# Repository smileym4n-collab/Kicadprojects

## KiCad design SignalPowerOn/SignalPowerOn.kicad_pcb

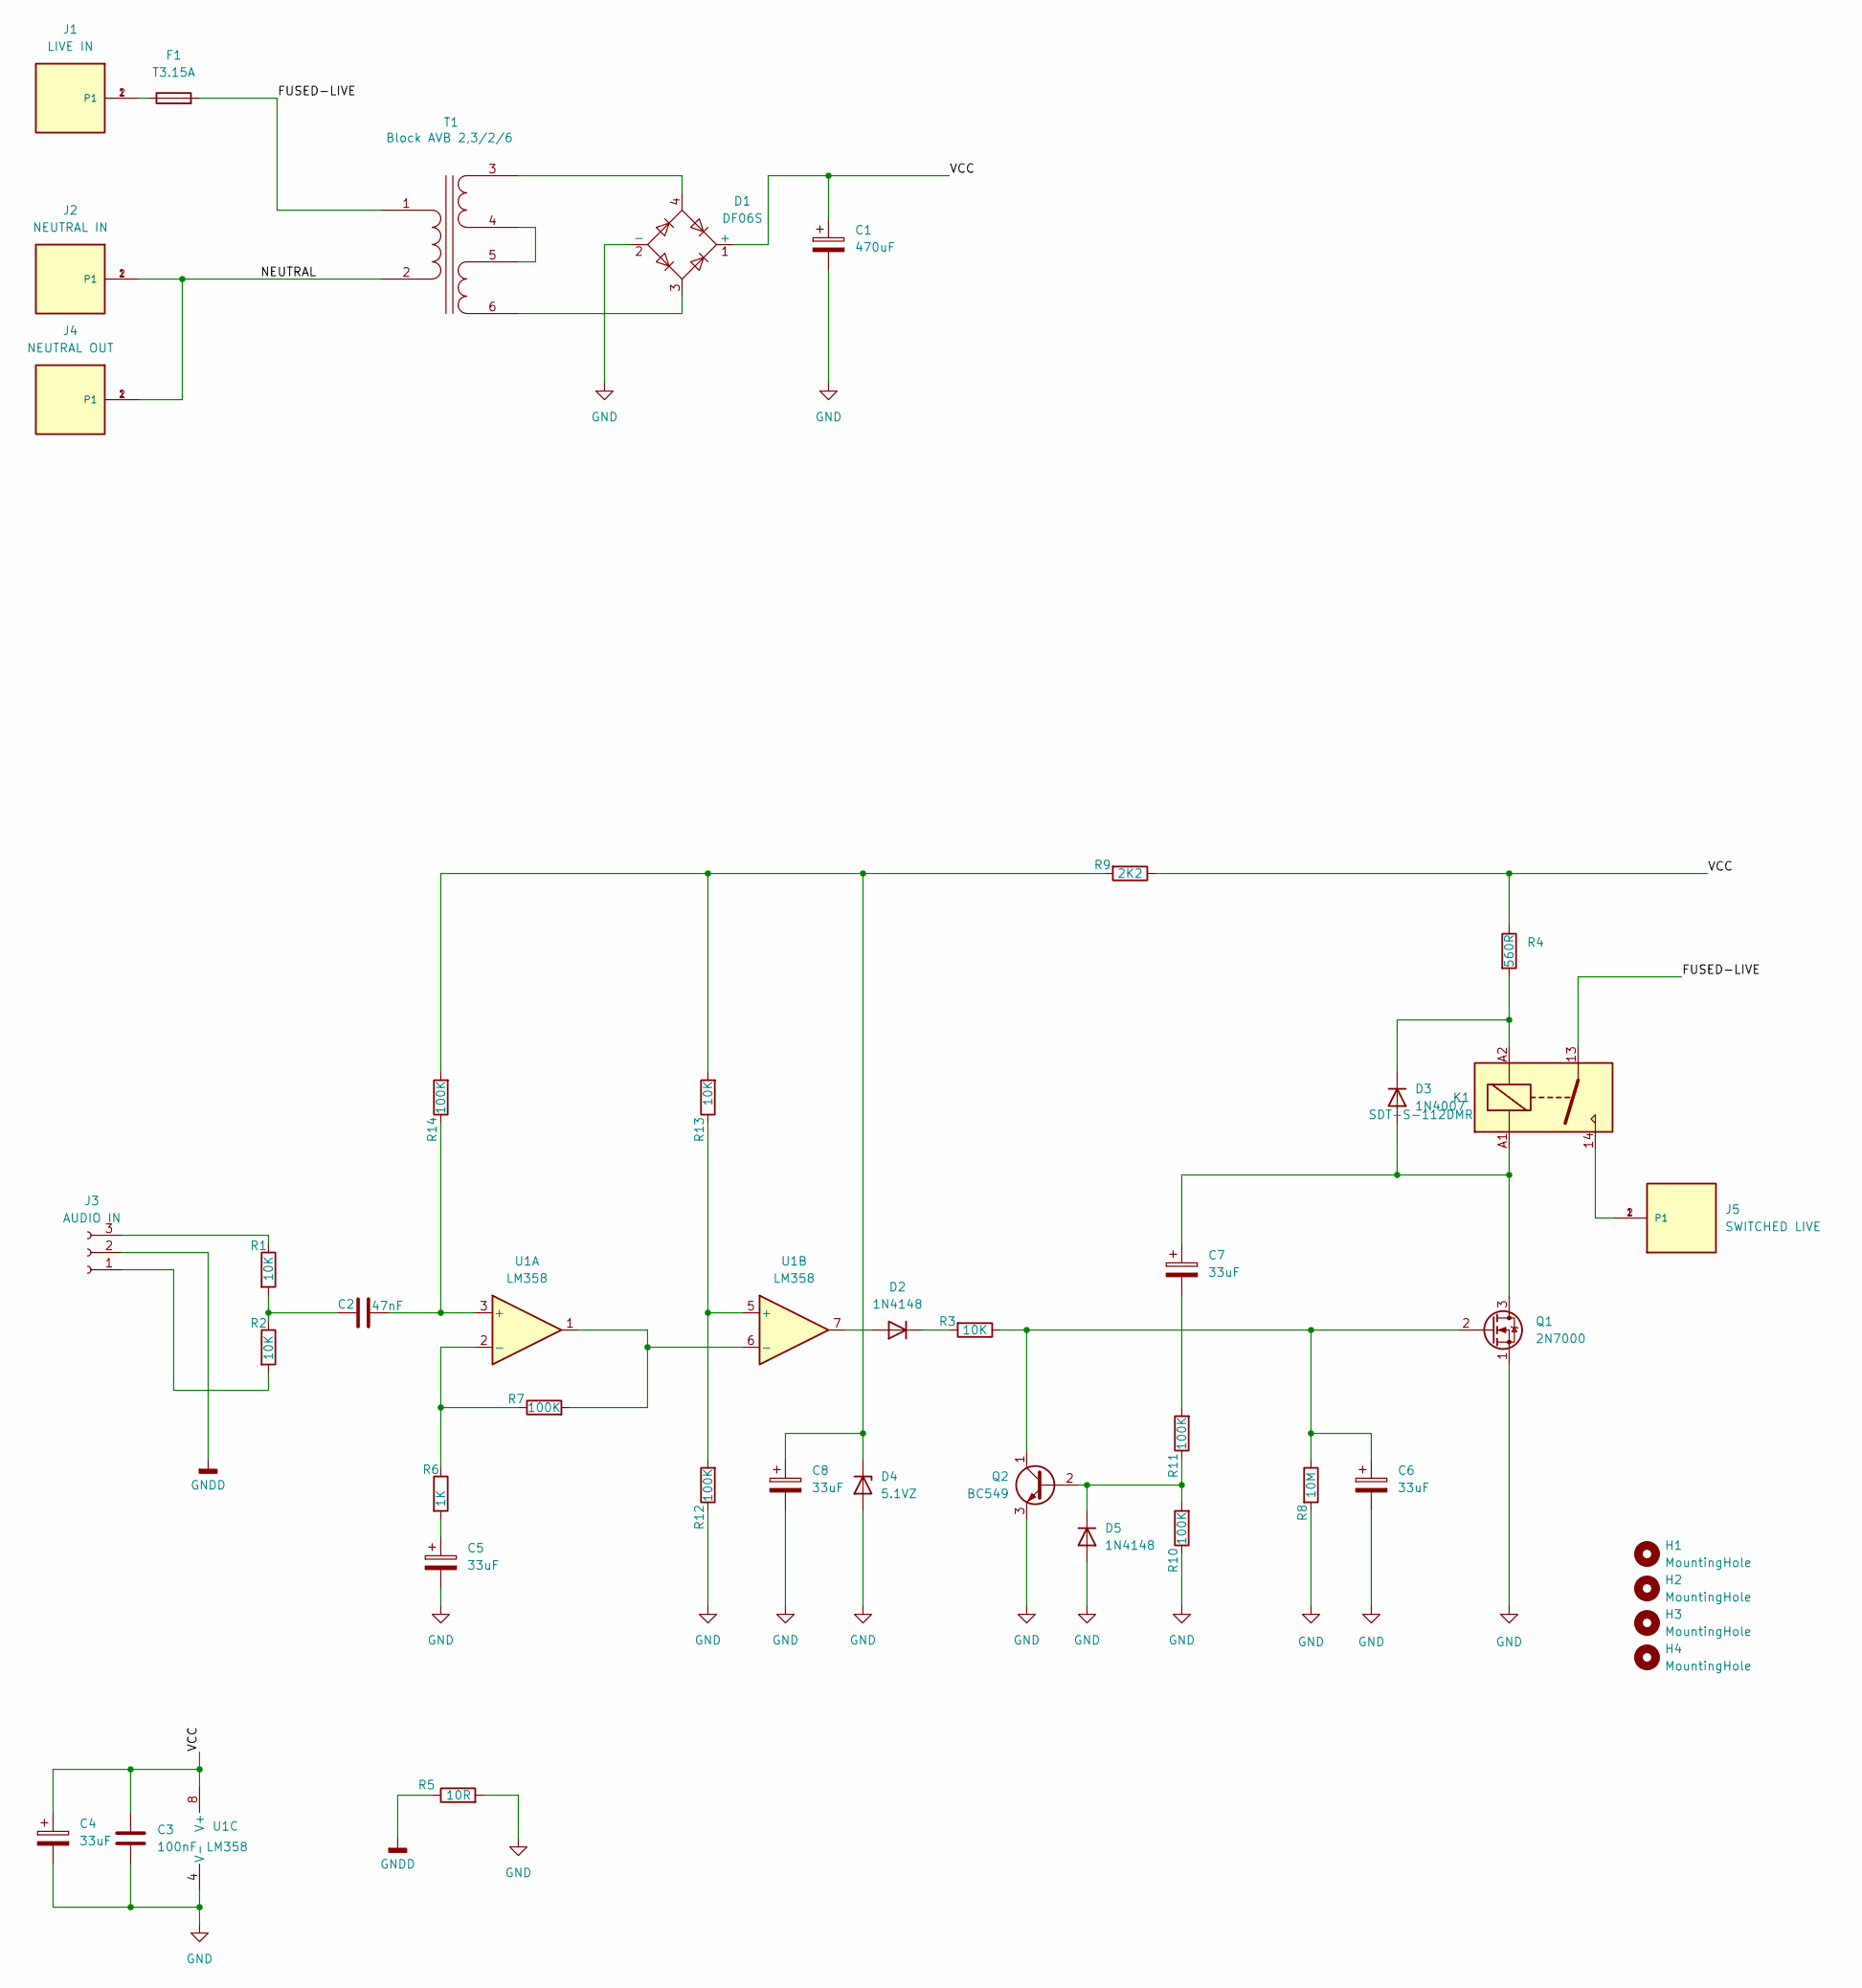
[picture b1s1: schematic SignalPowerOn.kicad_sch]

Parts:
C1: 470uF; CP_Radial_D10.0mm_P5.00mm
C2: 47nF; C_Rect_L7.0mm_W2.0mm_P5.00mm
C3: 100nF; C_1206_3216Metric_Pad1.33x1.80mm_HandSolder
C4, C5, C6, C7, C8: 33uF; CP_Radial_D5.0mm_P2.50mm
D1: DF06S; Diode_Bridge_OnSemi_SDIP-4L
D2, D5: 1N4148; D_DO-35_SOD27_P7.62mm_Horizontal
D3: 1N4007; D_DO-41_SOD81_P10.16mm_Horizontal
D4: 5.1VZ; D_DO-35_SOD27_P7.62mm_Horizontal
F1: T3.15A; Fuseholder_Cylinder-5x20mm_Schurter_0031_8201_Horizontal_Op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
H1, H2, H3, H4: MountingHole; MountingHole_4.3mm_M4
J1: LIVE IN; TE_62409-1; PART_DESCRIPTION CONN QC TAB 0.250 SOLDER
J2: NEUTRAL IN; TE_62409-1; PART_DESCRIPTION CONN QC TAB 0.250 SOLDER
J3: AUDIO IN; JST_XH_B3B-XH-A_1x03_P2.50mm_Vertical
J4: NEUTRAL OUT; TE_62409-1; PART_DESCRIPTION CONN QC TAB 0.250 SOLDER
J5: SWITCHED LIVE; TE_62409-1; PART_DESCRIPTION CONN QC TAB 0.250 SOLDER
K1: SDT-S-112DMR; Relay_SPST_Omron_G2RL-1A
Q1: 2N7000; TO-92L_Inline_Wide
Q2: BC549; TO-92L_Inline_Wide
R1, R2, R3, R13: 10K; R_0805_2012Metric_Pad1.20x1.40mm_HandSolder
R4: 560R; R_Axial_DIN0411_L9.9mm_D3.6mm_P12.70mm_Horizontal
R5: 10R; R_0805_2012Metric_Pad1.20x1.40mm_HandSolder
R6: 1K; R_0805_2012Metric_Pad1.20x1.40mm_HandSolder
R7, R10, R11, R12, R14: 100K; R_0805_2012Metric_Pad1.20x1.40mm_HandSolder
R8: 10M; R_0805_2012Metric_Pad1.20x1.40mm_HandSolder
R9: 2K2; R_0805_2012Metric_Pad1.20x1.40mm_HandSolder
T1: Block AVB 2,3/2/6; AVB2.326 Transformer
U1: LM358; DIP-8_W7.62mm

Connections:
/FUSED-LIVE: F1.2, K1.13, T1.1 (AA)
/NEUTRAL: J2.1, J2.2 (P1), J4.1, J4.2 (P1), T1.2 (AB)
/VCC: C1.1, C3.1, C4.1, D1.1 (+), R4.1, R9.1, U1.8 (V+)
GND: C1.2, C3.2, C4.2, C5.2, C6.2, C8.2, D1.2 (-), D4.2 (A), D5.2 (A), Q1.1 (S), Q2.3 (E), R5.2, R8.2, R10.1, R12.1, U1.4 (V-)
GNDD: J3.2, R5.1
unnamed: C2.1, R1.2, R2.1
unnamed: C5.1, R6.2
unnamed: C7.2, R11.2
unnamed: D2.2 (A), U1.7
unnamed: D2.1 (K), R3.2
unnamed: C7.1, D3.2 (A), K1.A1, Q1.3 (D)
unnamed: D3.1 (K), K1.A2, R4.2
unnamed: C8.1, D4.1 (K), R9.2, R13.2, R14.2
unnamed: D5.1 (K), Q2.2 (B), R10.2, R11.1
unnamed: F1.1, J1.1, J1.2 (P1)
unnamed: J3.1, R2.2
unnamed: J3.3, R1.1
unnamed: J5.1, J5.2 (P1), K1.14
unnamed: C6.1, Q1.2 (G), Q2.1 (C), R3.1, R8.1
unnamed: D1.4, T1.3 (SA)
unnamed: T1.4 (SB), T1.5 (SC)
unnamed: D1.3, T1.6 (SD)
unnamed: C2.2, R14.1, U1.3 (+)
unnamed: R6.1, R7.1, U1.2 (-)
unnamed: R12.2, R13.1, U1.5 (+)
unnamed: R7.2, U1.1, U1.6 (-)

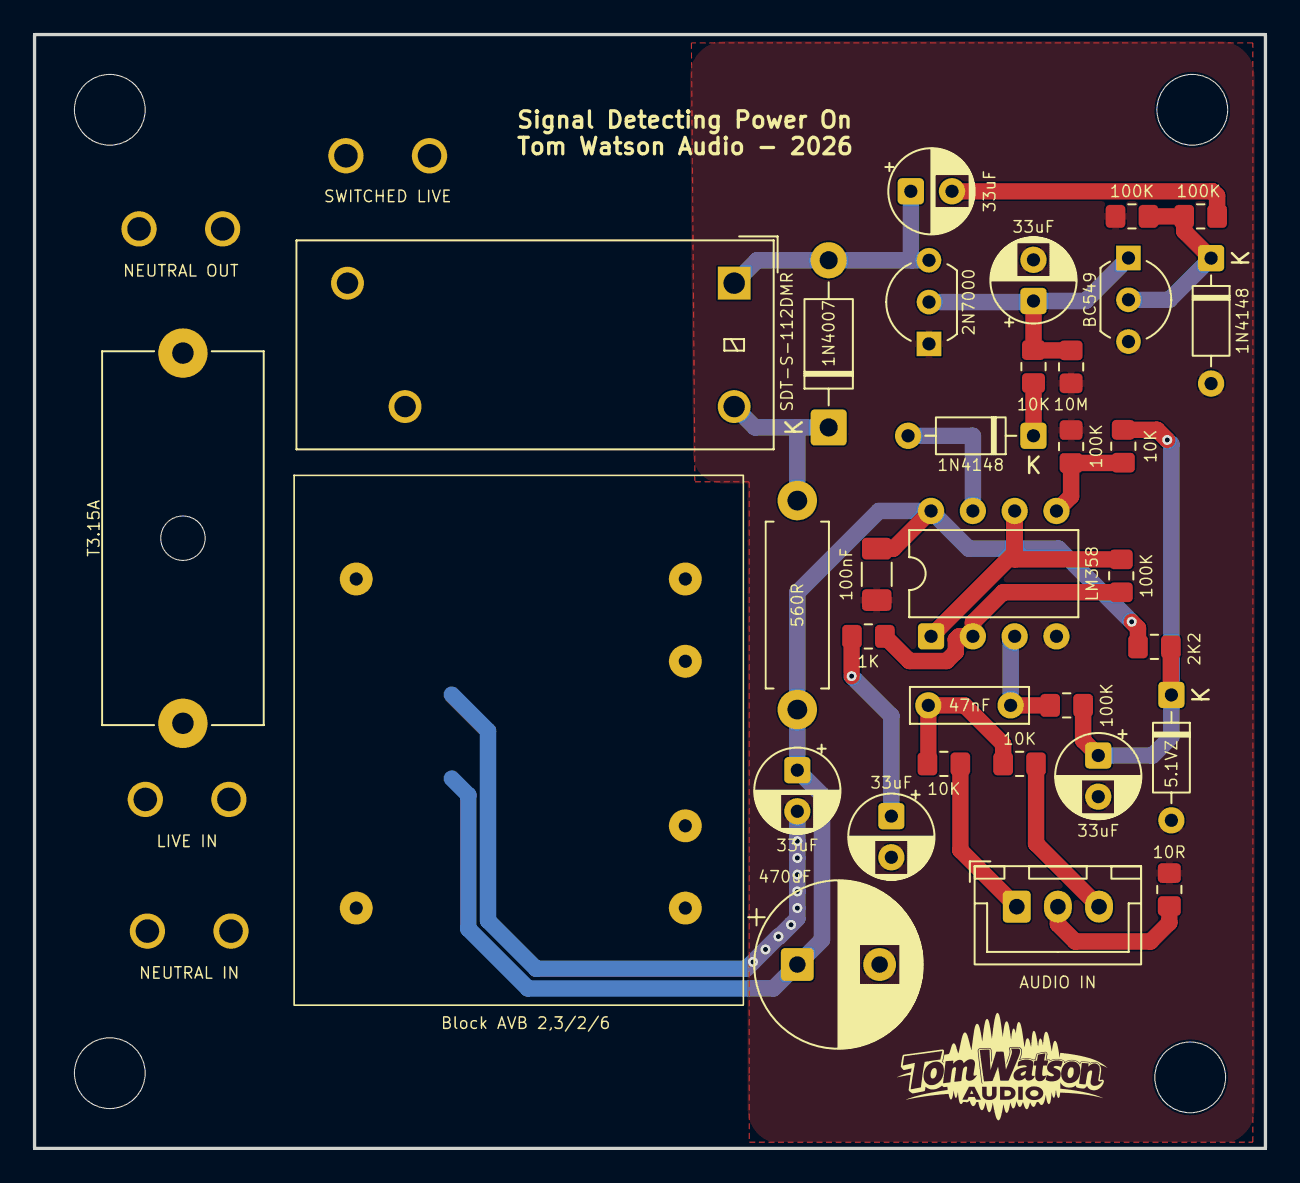
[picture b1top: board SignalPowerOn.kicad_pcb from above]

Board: 2 copper layers, 74.8 x 67.7 mm, 42 parts (1 on the bottom side), 26 nets.

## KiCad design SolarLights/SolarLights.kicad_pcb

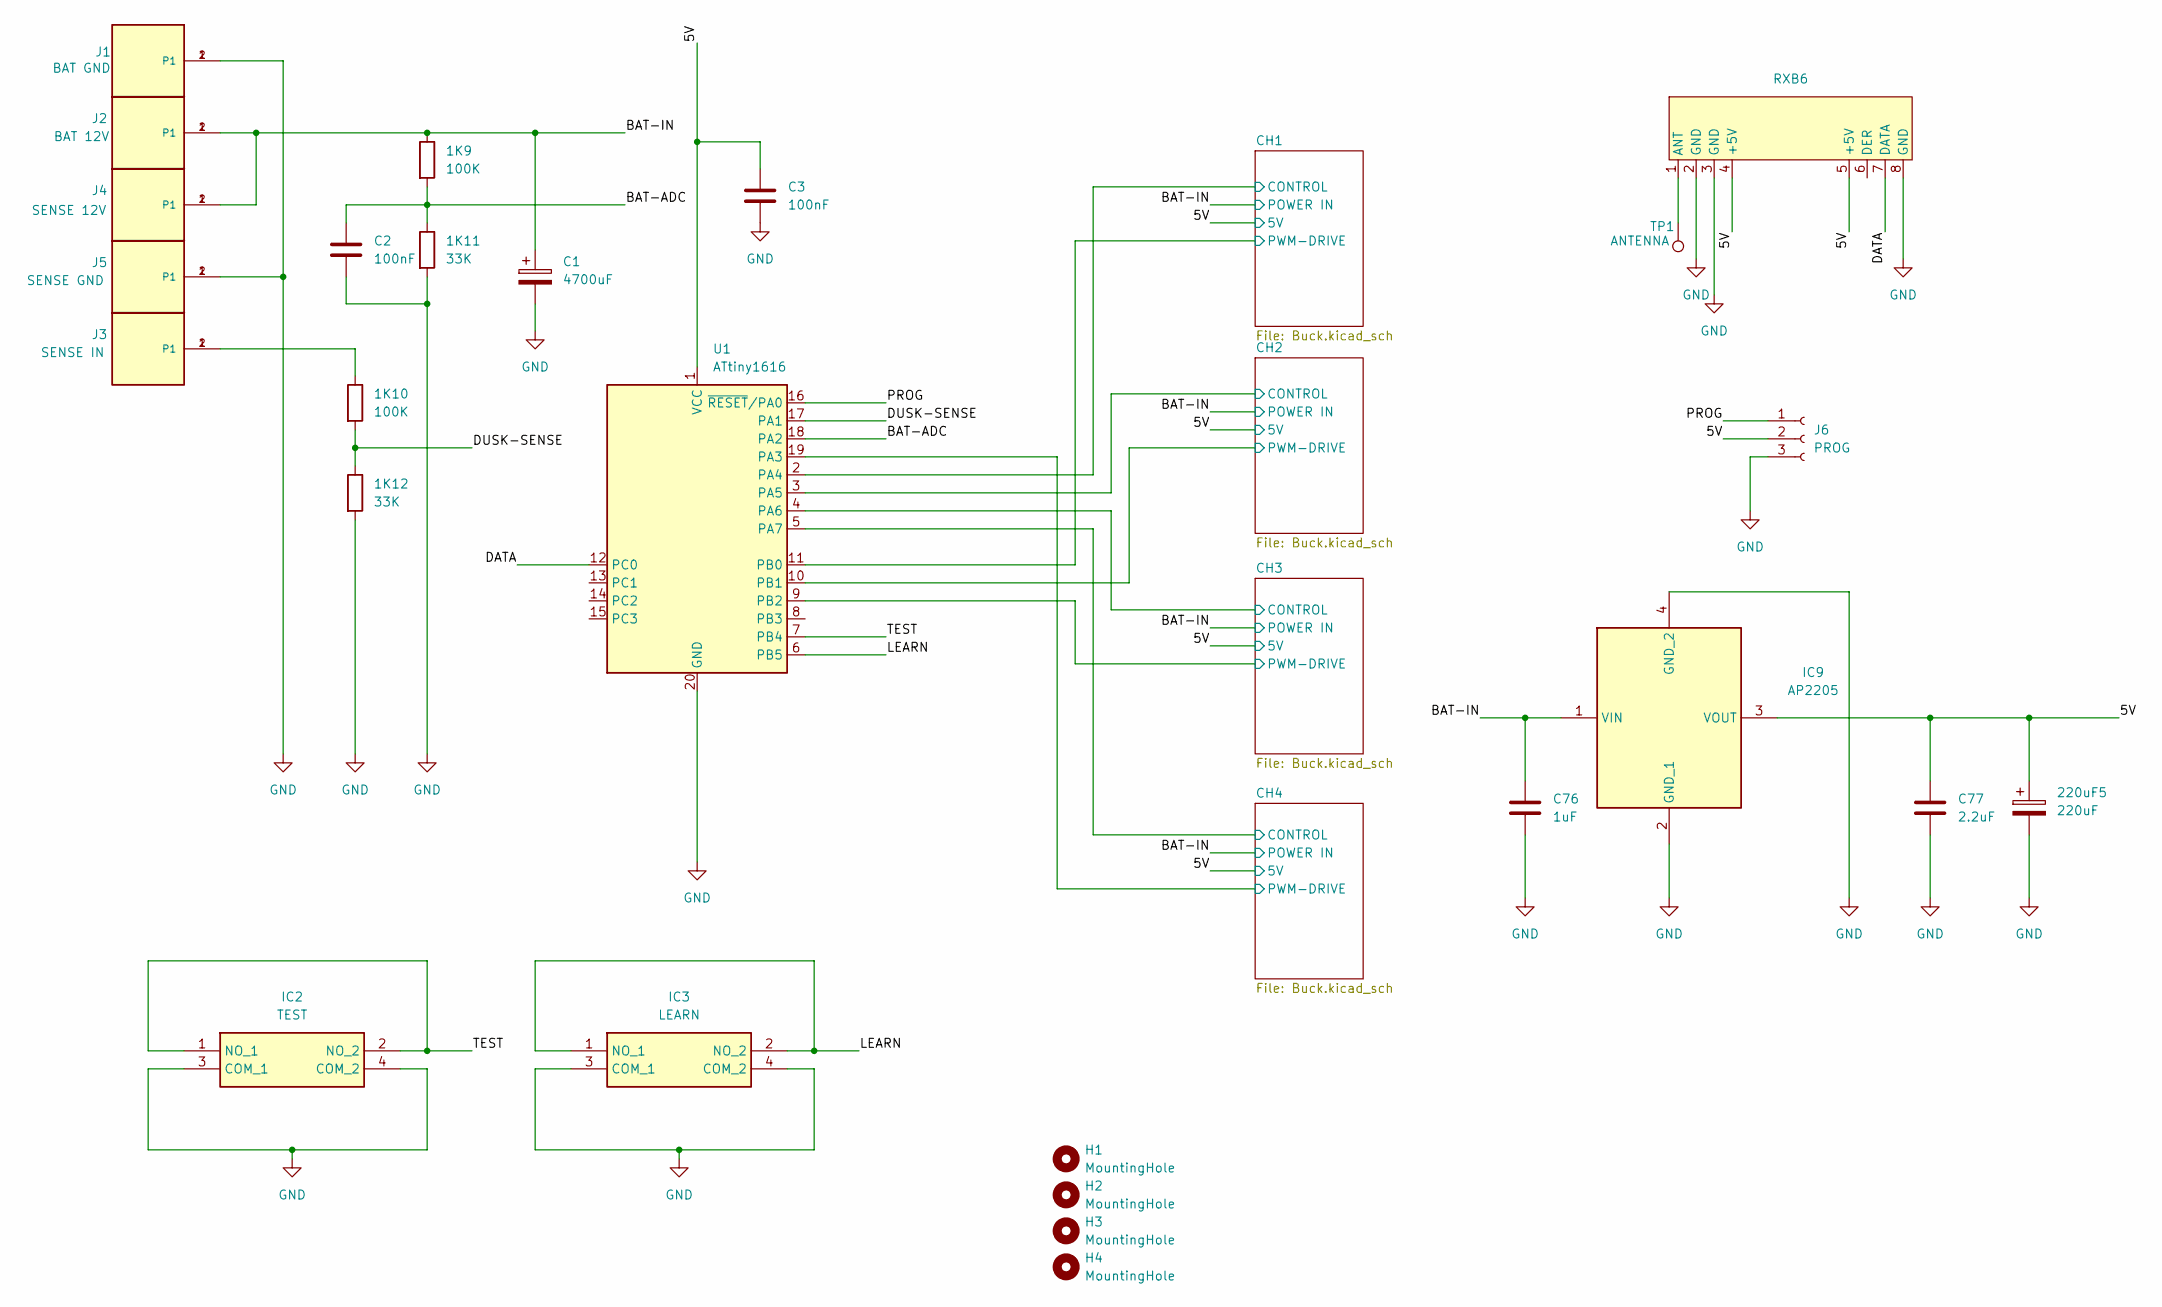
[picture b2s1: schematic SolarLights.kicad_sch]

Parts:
1K9, 1K10: 100K; R_0805_2012Metric_Pad1.20x1.40mm_HandSolder
1K11, 1K12: 33K; R_0805_2012Metric_Pad1.20x1.40mm_HandSolder
220uF5: 220uF; CP_Radial_D6.3mm_P2.50mm
C1: 4700uF; CP_Radial_D16.0mm_P7.50mm
C2, C3: 100nF; C_1206_3216Metric_Pad1.33x1.80mm_HandSolder
C76: 1uF; C_1206_3216Metric_Pad1.33x1.80mm_HandSolder
C77: 2.2uF; C_0805_2012Metric_Pad1.18x1.45mm_HandSolder
H1, H2, H3, H4: MountingHole; MountingHole_4mm
IC2: TEST; TS026650BK100SCRD; Mouser Part Number 179-TS026650BK100SCR
IC3: LEARN; TS026650BK100SCRD; Mouser Part Number 179-TS026650BK100SCR
IC9: AP2205; 2205; Mouser Part Number 621-AP2205-50YR-13
J1: BAT GND; TE_62409-1; PART_DESCRIPTION CONN QC TAB 0.250 SOLDER
J2: BAT 12V; TE_62409-1; PART_DESCRIPTION CONN QC TAB 0.250 SOLDER
J3: SENSE IN; TE_62409-1; PART_DESCRIPTION CONN QC TAB 0.250 SOLDER
J4: SENSE 12V; TE_62409-1; PART_DESCRIPTION CONN QC TAB 0.250 SOLDER
J5: SENSE GND; TE_62409-1; PART_DESCRIPTION CONN QC TAB 0.250 SOLDER
J6: PROG; JST_XH_B3B-XH-A_1x03_P2.50mm_Vertical
RXB6: RXB6
TP1: ANTENNA; TestPoint_Pad_D4.0mm
U1: ATtiny1616; SOIC-20W_7.5x12.8mm_P1.27mm

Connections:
/5V: 220uF5.1, C3.1, C77.1, IC9.3 (VOUT), J6.2, RXB6.4 (+5V), RXB6.5 (+5V), U1.1 (VCC); also elsewhere on the board
/BAT-ADC: 1K9.2, 1K11.1, C2.1, U1.18 (PA2)
/BAT-IN: 1K9.1, C1.1, C76.2, IC9.1 (VIN), J2.1, J2.2 (P1), J4.1, J4.2 (P1); also elsewhere on the board
/CH1/CONTROL: U1.2 (PA4); also elsewhere on the board
/CH1/PWM-DRIVE: U1.11 (PB0); also elsewhere on the board
/CH2/CONTROL: U1.3 (PA5); also elsewhere on the board
/CH2/PWM-DRIVE: U1.10 (PB1); also elsewhere on the board
/CH3/CONTROL: U1.4 (PA6); also elsewhere on the board
/CH3/PWM-DRIVE: U1.9 (PB2); also elsewhere on the board
/CH4/CONTROL: U1.5 (PA7); also elsewhere on the board
/CH4/PWM-DRIVE: U1.19 (PA3); also elsewhere on the board
/DATA: RXB6.7 (DATA), U1.12 (PC0)
/DUSK-SENSE: 1K10.2, 1K12.1, U1.17 (PA1)
/LEARN: IC3.1 (NO_1), IC3.2 (NO_2), U1.6 (PB5)
/PROG: J6.1, U1.16 (~RESET/PA0)
/TEST: IC2.1 (NO_1), IC2.2 (NO_2), U1.7 (PB4)
GND: 1K11.2, 1K12.2, 220uF5.2, C1.2, C2.2, C3.2, C76.1, C77.2, IC2.3 (COM_1), IC2.4 (COM_2), IC3.3 (COM_1), IC3.4 (COM_2), IC9.2 (GND_1), IC9.4 (GND_2), J1.1, J1.2 (P1), J5.1, J5.2 (P1), J6.3, RXB6.2 (GND), RXB6.3 (GND), RXB6.8 (GND), U1.20 (GND); also elsewhere on the board
unnamed: 1K10.1, J3.1, J3.2 (P1)
unnamed: RXB6.1 (ANT), TP1.1 (1_1)

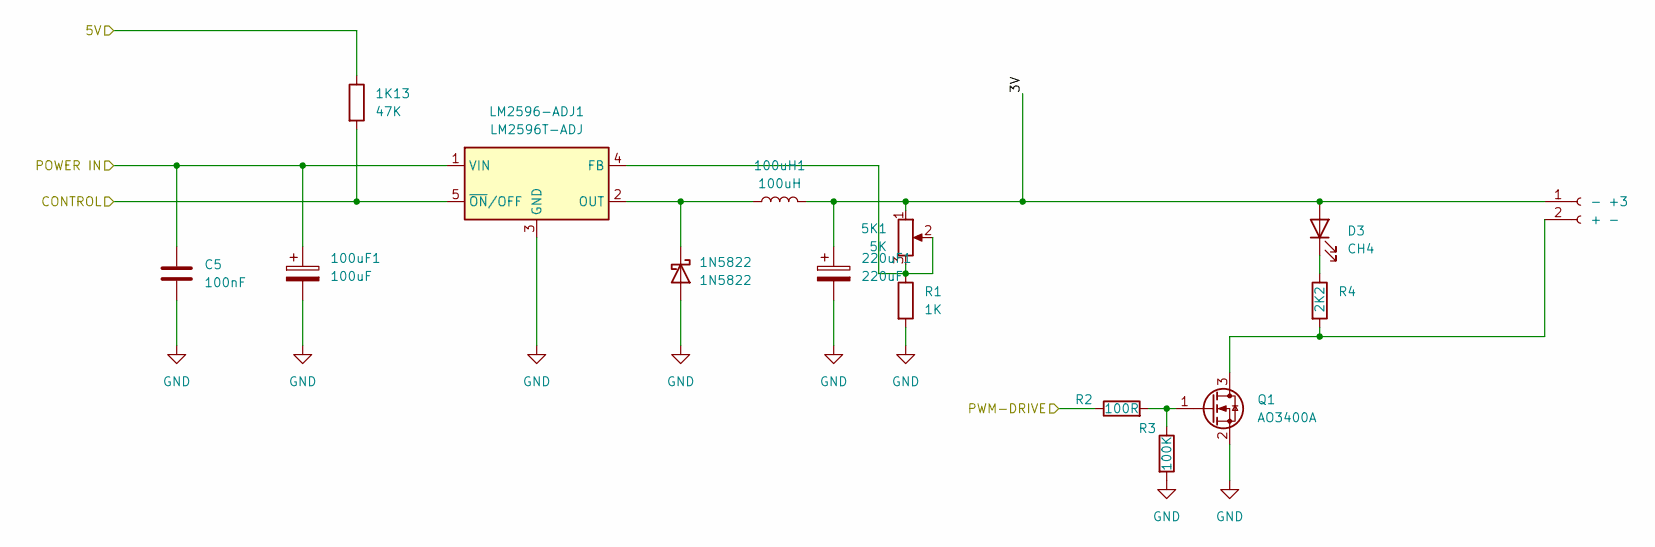
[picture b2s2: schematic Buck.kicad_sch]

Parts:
1K13: 47K; R_0805_2012Metric_Pad1.20x1.40mm_HandSolder
1N5822: 1N5822; D_DO-201AD_P15.24mm_Horizontal
5K1: 5K; Potentiometer_Vishay_T93YA_Vertical
100uF1: 100uF; CP_Radial_D8.0mm_P2.50mm
100uH1: 100uH; L_Radial_D10.5mm_P4.00x5.00mm_Murata_1200RS
220uF1: 220uF; CP_Radial_D6.3mm_P2.50mm
-   +3: + -; JST_XH_B2B-XH-A_1x02_P2.50mm_Vertical
C5: 100nF; C_1206_3216Metric_Pad1.33x1.80mm_HandSolder
D3: CH4; LED_D5.0mm
LM2596-ADJ1: LM2596T-ADJ; TO-220-5_P3.4x3.7mm_StaggerOdd_Lead3.8mm_Vertical
Q1: AO3400A; SOT-23
R1: 1K; R_0805_2012Metric_Pad1.20x1.40mm_HandSolder
R2: 100R; R_0805_2012Metric_Pad1.20x1.40mm_HandSolder
R3: 100K; R_0805_2012Metric_Pad1.20x1.40mm_HandSolder
R4: 2K2; R_0805_2012Metric_Pad1.20x1.40mm_HandSolder

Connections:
/5V: 1K13.1; also elsewhere on the board
/BAT-IN: 100uF1.1, C5.1, LM2596-ADJ1.1 (VIN); also elsewhere on the board
/CH1/3V: 5K1.1, 100uH1.2, 220uF1.1, - +3.1, D3.2 (A)
/CH1/CONTROL: 1K13.2, LM2596-ADJ1.5 (~ON/OFF); also elsewhere on the board
/CH1/PWM-DRIVE: R2.1; also elsewhere on the board
GND: 1N5822.2 (A), 100uF1.2, 220uF1.2, C5.2, LM2596-ADJ1.3 (GND), Q1.2 (S), R1.2, R3.2; also elsewhere on the board
unnamed: 1N5822.1 (K), 100uH1.1, LM2596-ADJ1.2 (OUT)
unnamed: - +3.2, Q1.3 (D), R4.2
unnamed: D3.1 (K), R4.1
unnamed: 5K1.2, 5K1.3, LM2596-ADJ1.4 (FB), R1.1
unnamed: Q1.1 (G), R2.2, R3.1

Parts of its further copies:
1K2, 1K3, 1K4: 1K; R_0805_2012Metric_Pad1.20x1.40mm_HandSolder
1K6, 1K7, 1K20: 100K; R_0805_2012Metric_Pad1.20x1.40mm_HandSolder
1K14, 1K15, 1K16: 47K; R_0805_2012Metric_Pad1.20x1.40mm_HandSolder
1K17, 1K18, 1K19: 2K2; R_0805_2012Metric_Pad1.20x1.40mm_HandSolder
1K22, 1K23, 1K24: 100R; R_0805_2012Metric_Pad1.20x1.40mm_HandSolder
1N5823, 1N5824, 1N5825: 1N5822; D_DO-201AD_P15.24mm_Horizontal
5K2, 5K3, 5K4: 5K; Potentiometer_Vishay_T93YA_Vertical
100uF2, 100uF3, 100uF4: 100uF; CP_Radial_D8.0mm_P2.50mm
100uH2, 100uH3, 100uH4: 100uH; L_Radial_D10.5mm_P4.00x5.00mm_Murata_1200RS
220uF2, 220uF3, 220uF4: 220uF; CP_Radial_D6.3mm_P2.50mm
-   +4, -   +5, -   +6: + -; JST_XH_B2B-XH-A_1x02_P2.50mm_Vertical
C6, C7, C8: 100nF; C_1206_3216Metric_Pad1.33x1.80mm_HandSolder
LM2596-ADJ2, LM2596-ADJ3, LM2596-ADJ4: LM2596T-ADJ; TO-220-5_P3.4x3.7mm_StaggerOdd_Lead3.8mm_Vertical
Q2, Q3, Q4: AO3400A; SOT-23

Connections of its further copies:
/5V: 1K14.1, 1K15.1, 1K16.1; also elsewhere on the board
/BAT-IN: 100uF2.1, 100uF3.1, 100uF4.1, C6.1, C7.1, C8.1, LM2596-ADJ2.1 (VIN), LM2596-ADJ3.1 (VIN), LM2596-ADJ4.1 (VIN); also elsewhere on the board
/CH2/3V: 5K2.1, 100uH2.2, 220uF2.1, - +4.1; also elsewhere on the board
/CH2/CONTROL: 1K14.2, LM2596-ADJ2.5 (~ON/OFF); also elsewhere on the board
/CH2/PWM-DRIVE: 1K22.1; also elsewhere on the board
/CH3/3V: 5K3.1, 100uH3.2, 220uF3.1, - +5.1; also elsewhere on the board
/CH3/CONTROL: 1K15.2, LM2596-ADJ3.5 (~ON/OFF); also elsewhere on the board
/CH3/PWM-DRIVE: 1K23.1; also elsewhere on the board
/CH4/3V: 5K4.1, 100uH4.2, 220uF4.1, - +6.1; also elsewhere on the board
/CH4/CONTROL: 1K16.2, LM2596-ADJ4.5 (~ON/OFF); also elsewhere on the board
/CH4/PWM-DRIVE: 1K24.1; also elsewhere on the board
GND: 1K2.2, 1K3.2, 1K4.2, 1K6.2, 1K7.2, 1K20.2, 1N5823.2 (A), 1N5824.2 (A), 1N5825.2 (A), 100uF2.2, 100uF3.2, 100uF4.2, 220uF2.2, 220uF3.2, 220uF4.2, C6.2, C7.2, C8.2, LM2596-ADJ2.3 (GND), LM2596-ADJ3.3 (GND), LM2596-ADJ4.3 (GND), Q2.2 (S), Q3.2 (S), Q4.2 (S); also elsewhere on the board
unnamed: 1N5823.1 (K), 100uH2.1, LM2596-ADJ2.2 (OUT)
unnamed: 1N5824.1 (K), 100uH3.1, LM2596-ADJ3.2 (OUT)
unnamed: 1N5825.1 (K), 100uH4.1, LM2596-ADJ4.2 (OUT)
unnamed: 1K17.2, - +4.2, Q2.3 (D)
unnamed: 1K18.2, - +5.2, Q3.3 (D)
unnamed: 1K19.2, - +6.2, Q4.3 (D)
unnamed 31: 1K17.1; also elsewhere on the board
unnamed 32: 1K18.1; also elsewhere on the board
unnamed 33: 1K19.1; also elsewhere on the board
unnamed: 1K2.1, 5K2.2, 5K2.3, LM2596-ADJ2.4 (FB)
unnamed: 1K3.1, 5K3.2, 5K3.3, LM2596-ADJ3.4 (FB)
unnamed: 1K4.1, 5K4.2, 5K4.3, LM2596-ADJ4.4 (FB)
unnamed: 1K6.1, 1K22.2, Q2.1 (G)
unnamed: 1K7.1, 1K23.2, Q3.1 (G)
unnamed: 1K20.1, 1K24.2, Q4.1 (G)

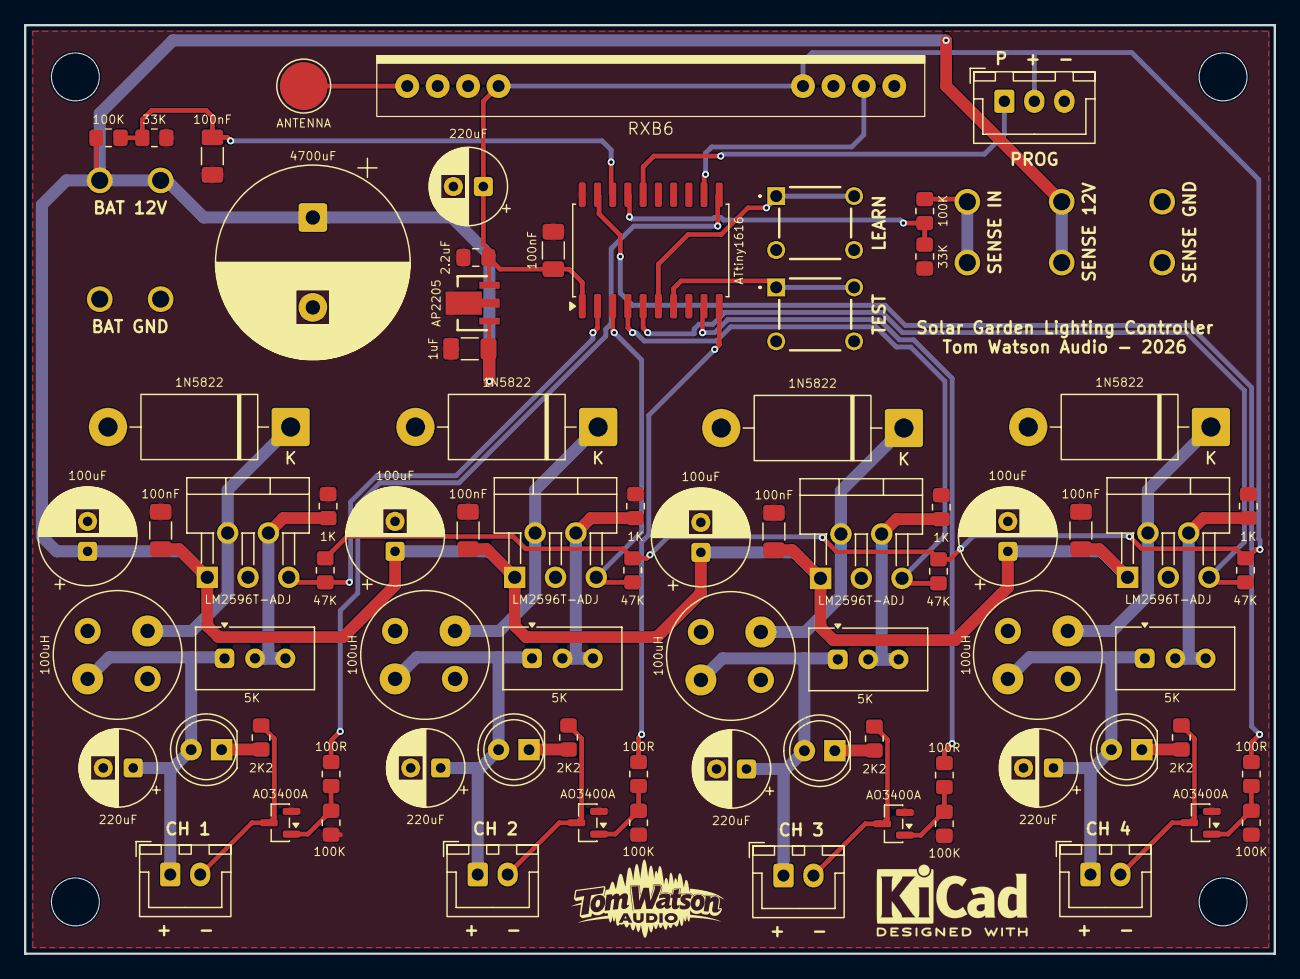
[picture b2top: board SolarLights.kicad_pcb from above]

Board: 2 copper layers, 104.3 x 77.5 mm, 86 parts (0 on the bottom side), 43 nets.

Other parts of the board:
D4: CH 2; LED_D5.0mm
D5: CH 3; LED_D5.0mm
D6: CH 4; LED_D5.0mm

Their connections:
/CH2/3V: D4.2 (A); also elsewhere on the board
/CH3/3V: D5.2 (A); also elsewhere on the board
/CH4/3V: D6.2 (A); also elsewhere on the board
unnamed 31: D4.1 (K); also elsewhere on the board
unnamed 32: D5.1 (K); also elsewhere on the board
unnamed 33: D6.1 (K); also elsewhere on the board

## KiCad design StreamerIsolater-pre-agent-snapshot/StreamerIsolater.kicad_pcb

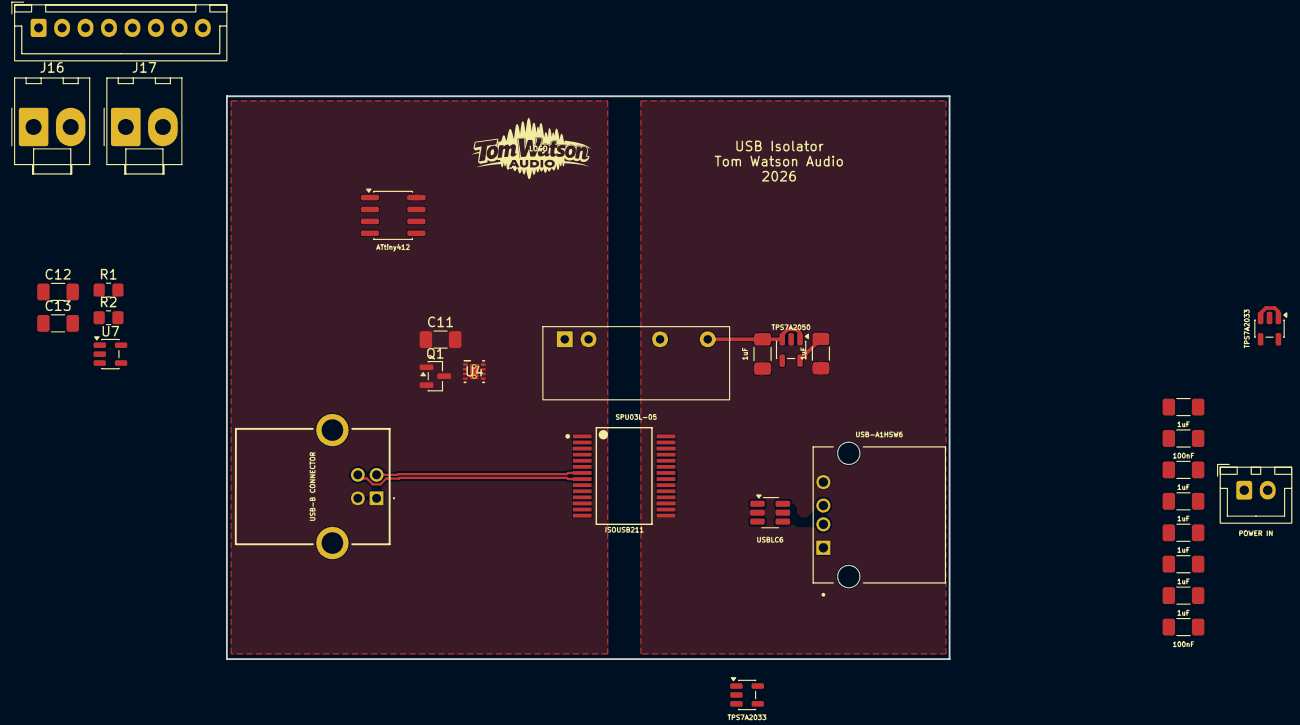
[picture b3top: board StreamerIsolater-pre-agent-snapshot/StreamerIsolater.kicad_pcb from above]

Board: 4 copper layers, 77.0 x 60.0 mm, 31 parts (0 on the bottom side), 22 nets.

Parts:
C1, C2, C3, C5, C6, C7, C8, C9, C12, C13: 1uF; C_1206_3216Metric_Pad1.33x1.80mm_HandSolder
C4, C10, C11: 100nF; C_1206_3216Metric_Pad1.33x1.80mm_HandSolder
IC2: USBLC6; SOT-23-6_Handsoldering
J1: USB-A1HSW6
J2: POWER IN; JST_XH_B2B-XH-A_1x02_P2.50mm_Vertical
J2#2: SYSTEM CONNECTOR; JST_XH_B8B-XH-A_1x08_P2.50mm_Vertical
J3: USB-B CONNECTOR; USBC
J16: POWER IN; Molex_KK-396_A-41791-0002_1x02_P3.96mm_Vertical
J17: PI POWER; Molex_KK-396_A-41791-0002_1x02_P3.96mm_Vertical
Q1: 2N7002; SOT-23
R1, R2: 100K; R_0805_2012Metric_Pad1.20x1.40mm_HandSolder
U1: ISOUSB211
U2: ATtiny412; SOIC-8_3.9x4.9mm_P1.27mm
U3: TPS7A2050; SOT-23-5
U4: TPS22975NDSGR; DSG0008B
U5, U6, U7: TPS7A2033; SOT-23-5
U10: SPU03L-05; SPU03L_05_SIP7

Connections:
/3V3-CLEAN: C8.1, C9.1, C10.1, U1.24 (VCC2), U1.27 (V3P3V2), U1.28 (VBUS2), U6.5 (OUT)
/3V3-DIRTY: C3.1, C4.1, C6.1, U1.1 (VBUS1), U1.2 (V3P3V1), U1.5 (VCC1), U5.5 (OUT)
/3V3-TINY: C11.1, C13.1, U2.1 (VCC), U7.5 (OUT)
/5V_SWITCHED: J17.2, U4.7 (VOUT), U4.8 (VOUT)
/PI_SAFE_TO_OFF: J2#2.6, R2.1, U2.7 (PA3)
/PI_SHUTDOWN_REQ: J2#2.7, Q1.3 (D)
/POWER-IN: C12.1, J2.2, J16.2, U4.1 (VIN), U4.2 (VIN), U4.4 (VBIAS), U7.1 (IN), U7.3 (EN)
/POWER_BUTTON: J2#2.4, U2.2 (PA6)
/STATUS_LED: J2#2.2, U2.3 (PA7)
/TPS_EN: R1.1, U2.4 (PA1), U4.3 (ON)
/UNREG-CLEAN: C2.1, C7.1, U3.1 (IN), U3.3 (EN), U6.1 (IN), U6.3 (EN), U10.7 (VOUT+)
/USB_PI_N: J3.2 (D-), U1.7 (UD-)
/USB_PI_P: J3.3 (D+), U1.8 (UD+)
/USB_XMOS_N1: IC2.3 (I/O2_1), U1.22 (DD-)
/USB_XMOS_N2: IC2.4 (I/O2_2), J1.2 (D-)
/USB_XMOS_P1: IC2.1 (I/O1_1), U1.21 (DD+)
/USB_XMOS_P2: IC2.6 (I/O1_2), J1.3 (D+)
/XMOS-VBUS: C1.1, IC2.5 (VBUS), J1.1 (VBUS), U3.5 (OUT)
GND: C1.2, C2.2, C3.2, C4.2, C5.2, C6.2, C7.2, C8.2, C9.2, C10.2, C12.2, C13.2, IC2.2 (GND), J1.4 (GND), U1.17 (GND2), U1.26 (GND2), U3.2 (GND), U5.2 (GND), U6.2 (GND), U7.2 (GND), U10.5 (VOUT-)
GNDD: C11.2, J2.1, J2#2.1, J2#2.3, J2#2.5, J3.4 (GND), J16.1, J17.1, Q1.2 (S), R1.2, R2.2, U1.3 (GND1), U1.12 (GND1), U2.8 (GND), U4.5 (GND), U4.9 (PAD), U10.2 (VIN-)
unnamed: Q1.1 (G), U2.5 (PA2)
unnamed: C5.1, U5.1 (IN), U5.3 (EN)
